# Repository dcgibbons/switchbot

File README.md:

jeepbot
=======

Jeep Bot - an intelligent accessory control system for Jeep Wranglers

In this proof of concept, the sketch assumes the following hardware has been 
configured:

  * An Arduino board with hardware SPI (any)
  * A Microchip mcp2515 CAN controller interface, such as the CAN-BUS
    shield from https://www.sparkfun.com/products/10039, wired to SPI
  * A SN74HC595 or compatible 8-bit shift register wired to SPI
  * An eight-or-more channel relay module, such as this one from http://www.sainsmart.com/8-channel-dc-5v-relay-module-for-arduino-pic-arm-dsp-avr-msp430-ttl-logic.html, that can be driven directly from GPIO logic

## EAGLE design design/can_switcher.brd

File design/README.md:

# Switchbot - The Smart Automotive Switching System (SASS)

## Overview

The "Switchbot" project is a smart switching system for automotive accessories. Imagine
having your off-road lights automatically controlled by your high-beams, or your aftermarket
LED headlights directly powered without special wiring harnesses, elimating both flicker and
swiching delays. Imagine having additional interior lighting or accessories automatically
activated whenever the car is switched on, or when the night-time interior lights are activated
by the vehicle. Imagine doing all of this without splicing any of the existing wiring. Switchbot
will do all of this, and more.

### Why is This Even Needed?

Utility vehicles frequently have many accessories installed by the owner or by vendors. These
accessories include additional lighting, recovery equipment (i.e. winches), sirens, 
radio/communication equipment, etc. Frequently, these accessories are installed by splicing
into the vehicle's own electrical wiring, which ultimately can cause system failure as 
connections fail and corrode over time. In an off-road environment, this situation is accelerated
by the harsh conditions.

In addition, vehicles today have complex electrical systems. Much of the vehicle's systems
communicate to one another using networking technologies such as a CAN bus or a LIN bus. These
networking systems cannot be used directly without adversing affecting the vehicle's operation.

Some vehicle manufacturers provide "upfitter" modules that are designed specifically for the
purpose of controlling aftermarket accessories. However, these seem to be currently limited 
only to truck vehicles, and not for off-road sport vehicles.

The marketplace has answered by providing accessory controllers that isolate the vehicle's
electrical system from accessories. Unfortunately, these modules completely isolate themselves
from the vehicle's electrical system, providing no integration features, such as automatic
light control.

The "switchbot" project aims to fill this hole in the marketplace with an intelligent and
integrated accessory control system. Initially this system will be aimed for the Jeep
Wrangler using the JK/JKU platform.

## Design

The production design of "Switchbot" will separate the system into the following primary modules:

1. A power/relay module - located in the engine bay, this module directly powers your accessories
using standard automotive relays and is the central wiring hub. Directly connected to the 
vehicle battery, it isolates all accessories from the vehicle's own electrical system.
2. A manual switch module - an optional module that provides physical switches for master overrides
for each accessory.
3. The Switchbot module - an optional module that integrates with the vehicle's electrical system
and operates accessories based on vehicle activity and user configuration.
4. Touch-screen - an optional module that provides a touch-screen interface for switches instead
of manual switches.

This design approach fulfills the following requirements for both hobbist and commerical
productization:

1. Lower price points by separating advanced features from the basics.
2. Lower price points by allowing different numbers of accessory connections in the power/relay
module. For example, the lower price module may only contain 4 switches, whereas the deluxe
module may include 8 or more.
3. Isolating vehicle-specific interfacing and software into a single module, separate from
the power/delay module, allowing easy multi-vehicle support in the future.
4. The unintelligent power/relay module can be used to provide users with their own basic
switching platform, with additional reliability and flexibility compared to the typical homegrown
solution.

### Power/Relay Module Design Considerations

The power/relay module is the hub that all aftermarket accessories will connect to. This 
module will provide each accessory connectin with an individualy fused power and ground
connection. Power to each accessory will be controlled by an external switching module.
The power/relay module will be directly connected to the battery, via a master breaker,
completely isolating accessories from the rest of the vehicle's electrical system.

The power/relay module is the simplest of all the modules in the smartbot system, but has
the most expensive components and the highest environmental demands due to its location
in the engine compartment. 

Automotive-class relays tend to be relatively expensive, ranging from $1.50 to $7.50 each.
Solid-state relays are not yet an option, as they are both too expensive and general, and
provide very limited options for high current (25a, 30a, or 40a load) applications.

While not required in the initial release of the module, the power/relay board will
include additional features such as a low-voltage cutoff circuit to prevent the vehicle's
battery from being drained.

### Switchbot Module Design Considerations

The switchbot module is ultimately a micro-controller that interfaces with the power/relay
module and with the vehicle's own communication network. On the JK platform, this means
the module should communicate to the CAN interior bus, and potentially the powertrain CAN
bus, so that it can detect when certain vehicle systems are activated, e.g. the headlamps.

Many modern micro-controllers targetted at the automotive market include CAN and/or LIN
interfaces, such as the Microchip PIC18 or the Texas Instruments C2000 families. As of
this writing, however, these MCUs are typically not cheaper than a multi-chip system
built around an MCU and a combination of a CAN controller and transceiver. Additionally,
all of the prototyping and research work has been done using ATMEGA MCUs, using the
Arduino platform, and Microchip's MCP2515 and MCP2551 CAN ICs. In the initial versions
of the smartbot system, the ATMEGA 328, the MCP2515, and the MCP2551 will be used
to lower the overall risk of the project. Future versions of find cost savings,
enhanced reliability, and increased CPU power by moving to an all-in-one MCU solution.

The JK platform has three CAN busses: the diagnostic CAN bus, the powertrain CAN bus,
and the interior CAN bus. All three busses terminate in the vehicle's TIPM module,
located in the engine compartment. While desierable, it is not practical to interface
with the busses via this module as the wiring terminals are water-resistent and 
complex.

There are two likely approaches for intefacing with the vehicle from the cabin: using
the diagnostic bus or the CAN interior bus. At first glance, the diagnostic bus would
appear ideal, but is not designed for long-running embedded applications. Additionally,
reverse engineering the necessary information available over the bus is highly time
consuming. Purchasing the same information directly from the manufacturer is out of
the range of a hobbist project, nor would it enable the project to be open-sourced.

Left with the CAN interior bus, we find that all of the information we are after is
directly available. The JK's EMIC module communicates all user activated features
to the TIPM. If the user or ambient light sensor wants the headlights on, the EMIC
makes it happen by telling the TIPM over the CAN interior bus. Switchbot can spy on
these messages and activate its own switches as needed.

The switchbot module must communicate to the power/relay module to activate each
individual accessory as needed. Two alternatives have been considered for this
communication:

1. Using a private communication channel, such as another CAN bus, between an MCU
on the power/relay module and an MCU on the switchbot module.
2. Individual switch signals to drive the relays in the power/relay module.

For the initial version, individual switch signals will be used to simplify the overall
system design and to keep costs down. Each switch signal is driven by an opticoupler 
which is in turned driven by the MCU (via a shift register IC). This will isolate the
MCU's 5v system from the 12v system needed to drive the automotive grade relays.

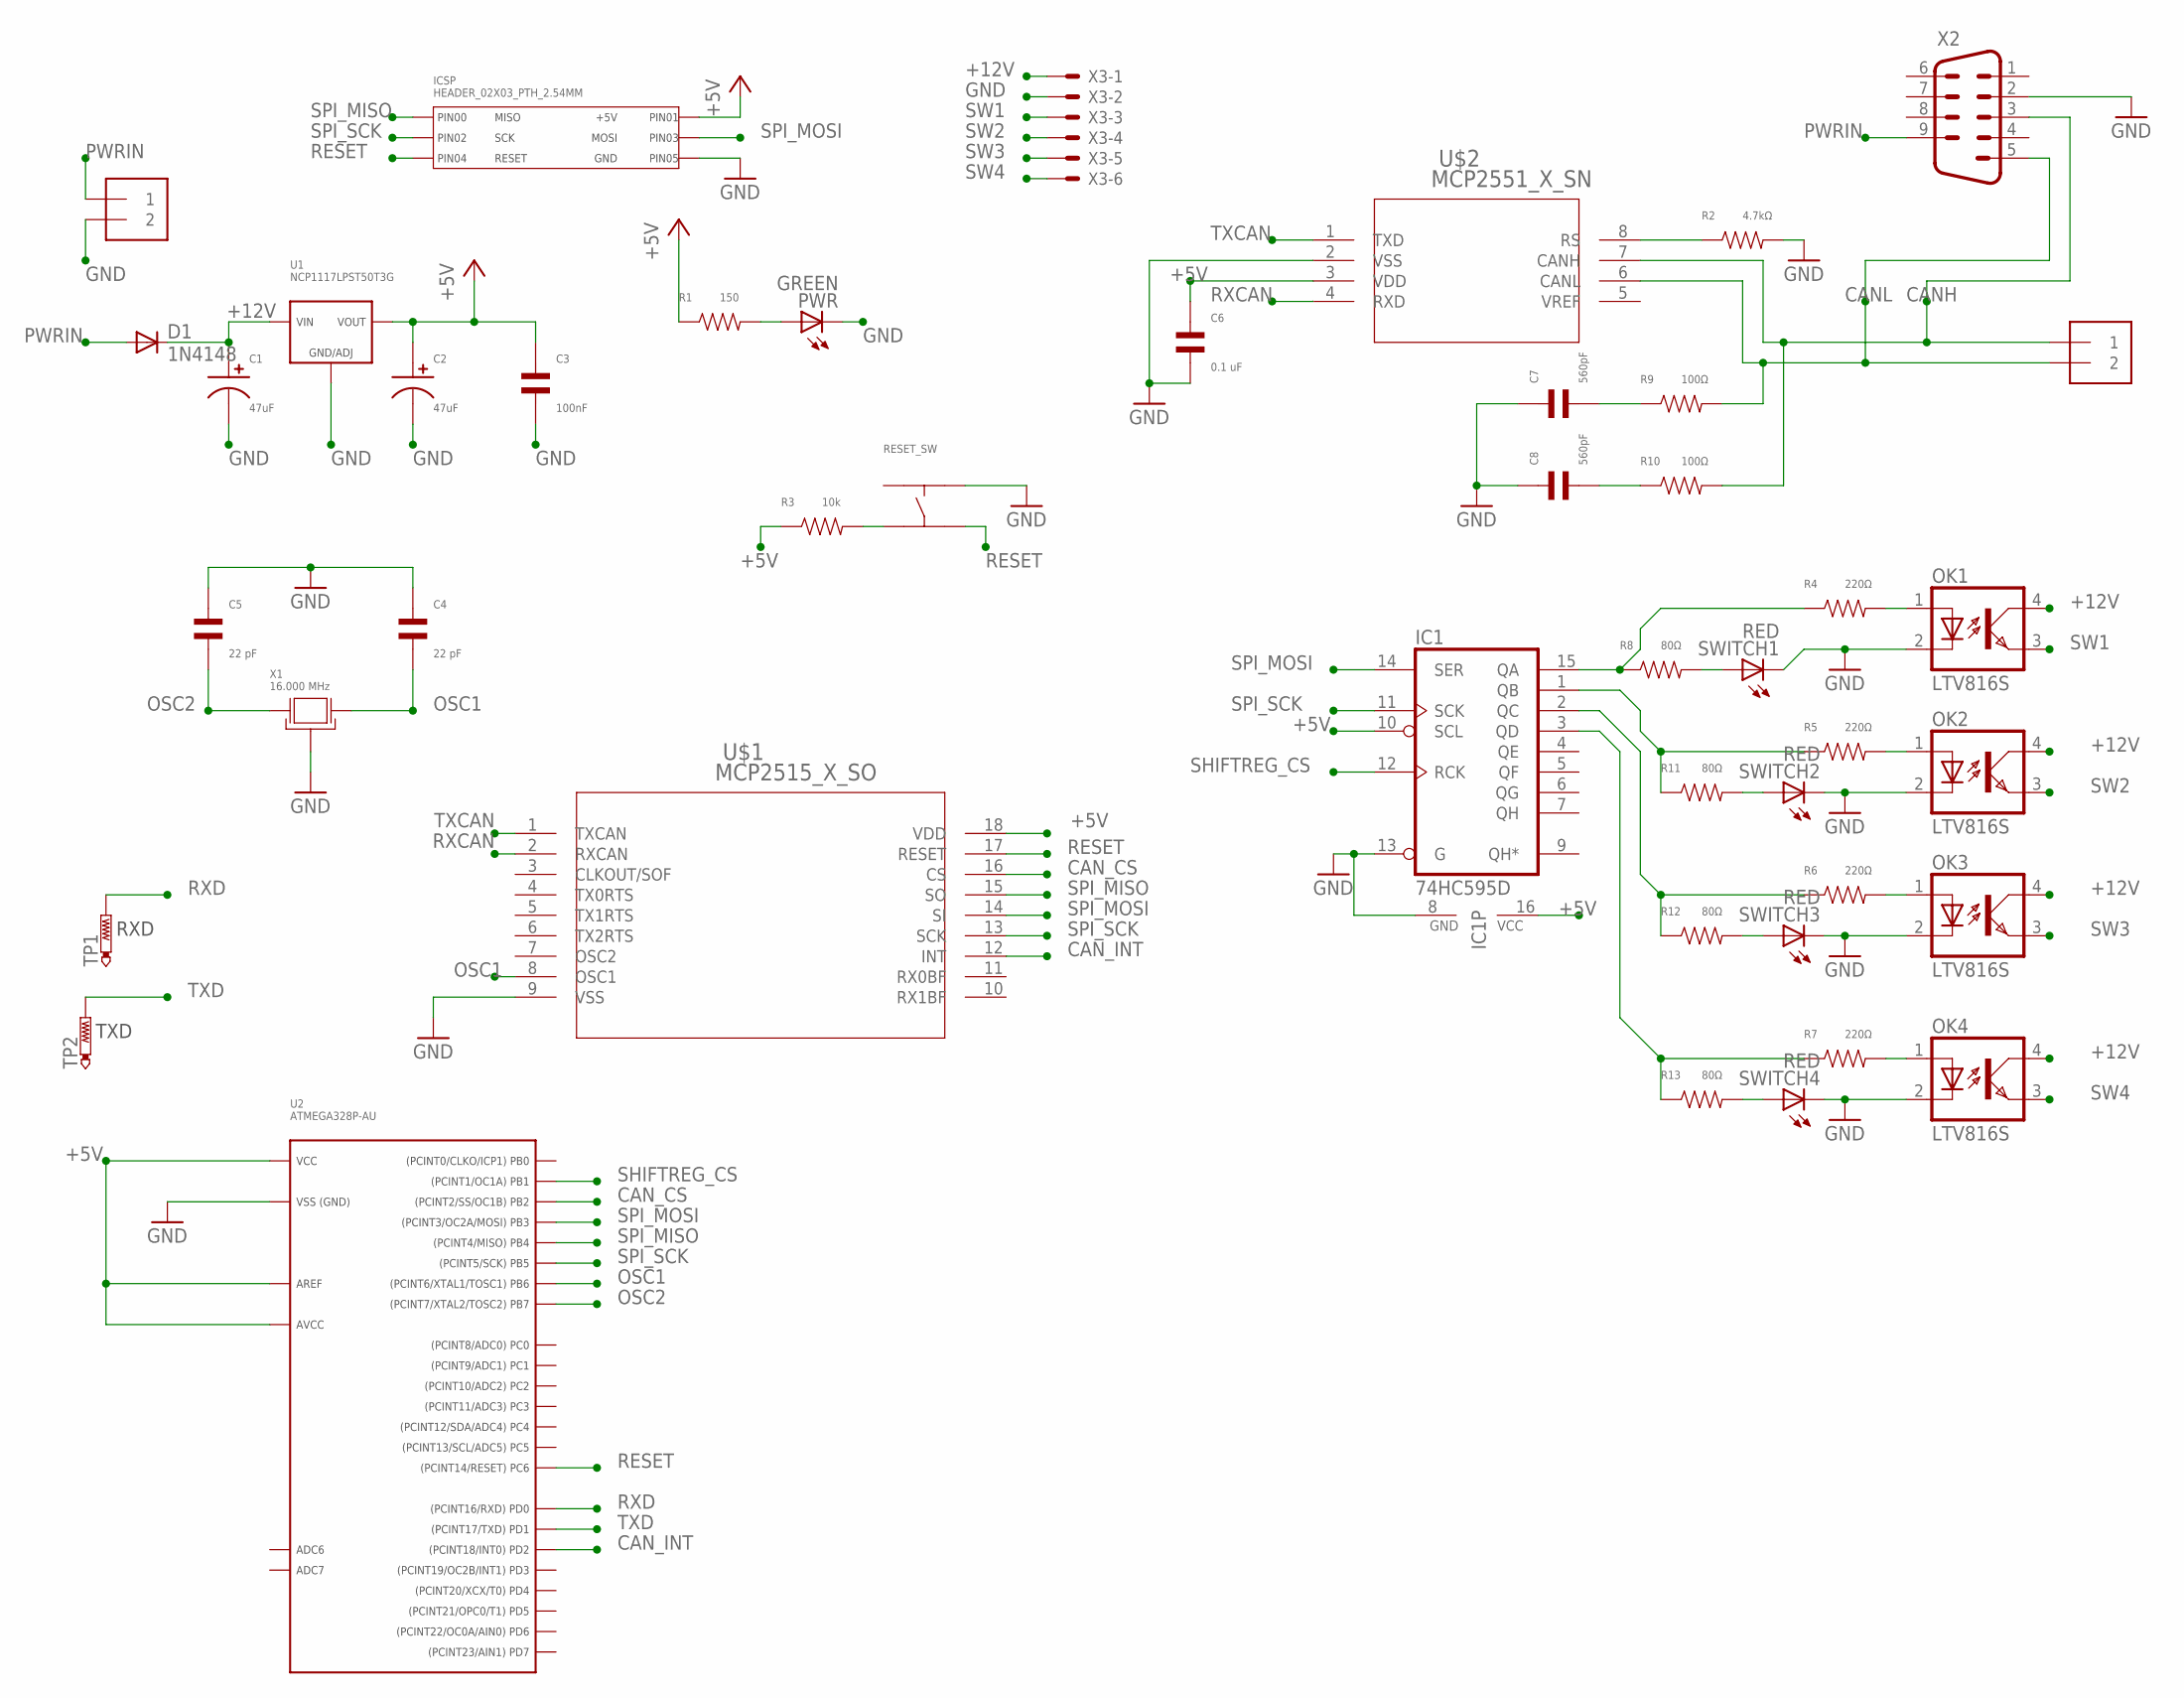
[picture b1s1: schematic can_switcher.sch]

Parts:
C1, C2: 47uF; CP6.3MM; MFG# MF-CAP-6.3MM-47uF
C3: 100nF; C0603
C4, C5: 22 pF; C0603
C6: 0.1 uF; C0603
C7, C8: 560pF; C0603; MFG# C0603C561J5GACTU
CANBUS: 1X2-3.5MM
D1: 1N4148; SMB
IC1: 74HC595D; SO16
ICSP: HEADER_02X03_PTH_2.54MM; PTH_2.54MM_02X03
J3: 1X2-3.5MM
OK1, OK2, OK3, OK4: LTV816S; SMD4; MPN LTV-816S-TA
PWR: GREEN; SML0603
R1: 150; R0603; MFG# RC0603FR-07150RL
R2: 4.7kΩ; R0603
R3: 10k; R0603
R4, R5, R6, R7: 220Ω; R0603
R8, R11, R12, R13: 80Ω; R0603
R9, R10: 100Ω; R0603
RESET_SW: TACT_6MM; TACT6MM; MFG# MF-SW-TACT-6MM
SWITCH1, SWITCH2, SWITCH3, SWITCH4: RED; SML0603
TP1, TP2: PTR1B1,27; B1,27
U1: NCP1117LPST50T3G; SOT-223-3
U2: ATMEGA328P-AU; TQFP32
U$1: MCP2515_X_SO; SOIC18_W_MC
U$2: MCP2551_X_SN; SOIC8_N_MC
X1: 16.000 MHz; 5MMX3.2MM; MFG# ASFL1-16.000MHZ-EC-T
X2: M09HP; MPN L717SDE09P1ACH
X3: 22-23-2061

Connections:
+5V: C2.P$1, C3.P$1, C6.P$1, IC1.10 (SCL), IC1.16 (VCC), ICSP.P$2 (PIN1), R1.P$1, R3.P$1, U1.P$1 (VOUT), U1.P$3 (VOUT), U2.P$4 (VCC), U2.P$6 (VCC), U2.P$18 (AVCC), U2.P$20 (AREF), U$1.18 (VDD), U$2.3 (VDD)
+12V: C1.P$1, D1.C, OK1.4 (COL), OK2.4 (COL), OK3.4 (COL), OK4.4 (COL), U1.P$4 (VIN), X3.1
CANH: CANBUS.1, R10.P$2, U$2.7 (CANH), X2.3
CANL: CANBUS.2, R9.P$2, U$2.6 (CANL), X2.5
CAN_CS: U2.P$14 (PB2), U$1.16 (CS)
CAN_INT: U2.P$32 (PD2), U$1.12 (INT)
GND: C1.P$2, C2.P$2, C3.P$2, C4.P$1, C5.P$1, C6.P$2, C7.P$1, C8.P$1, IC1.8 (GND), IC1.13 (G), ICSP.P$6 (PIN5), J3.2, OK1.2 (C), OK2.2 (C), OK3.2 (C), OK4.2 (C), PWR.C, R2.P$2, RESET_SW.P$2, SWITCH1.C, SWITCH2.C, SWITCH3.C, SWITCH4.C, U1.P$2 (GND/ADJ), U2.P$3 (GND), U2.P$5 (GND), U2.P$21 (GND), U$1.9 (VSS), U$2.2 (VSS), X1.P$2 (GND), X1.P$4 (GND), X2.2, X3.2
unnamed: PWR.A, R1.P$2
unnamed: R2.P$1, U$2.8 (RS)
unnamed: R3.P$2, RESET_SW.P$3
unnamed: R8.P$2, SWITCH1.A
unnamed: R11.P$2, SWITCH2.A
unnamed: R12.P$2, SWITCH3.A
unnamed: R13.P$2, SWITCH4.A
unnamed: OK4.1 (A), R7.P$2
unnamed: OK3.1 (A), R6.P$2
unnamed: OK2.1 (A), R5.P$2
unnamed: OK1.1 (A), R4.P$2
unnamed: IC1.15 (QA), R4.P$1, R8.P$1
unnamed: IC1.1 (QB), R5.P$1, R11.P$1
unnamed: IC1.2 (QC), R6.P$1, R12.P$1
unnamed: IC1.3 (QD), R7.P$1, R13.P$1
unnamed: C7.P$2, R9.P$1
unnamed: C8.P$2, R10.P$1
OSC1: C4.P$2, U2.P$7 (PB6), U$1.8 (OSC1), X1.P$3 (X1)
OSC2: C5.P$2, U2.P$8 (PB7), X1.P$1 (X0)
PWRIN: D1.A, J3.1, X2.9
RESET: ICSP.P$5 (PIN4), RESET_SW.P$4, U2.P$29 (PC6), U$1.17 (RESET)
RXCAN: U$1.2 (RXCAN), U$2.4 (RXD)
RXD: TP1.TP, U2.P$30 (PD0)
SHIFTREG_CS: IC1.12 (RCK), U2.P$13 (PB1)
SPI_MISO: ICSP.P$1 (PIN0), U2.P$16 (PB4), U$1.15 (SO)
SPI_MOSI: IC1.14 (SER), ICSP.P$4 (PIN3), U2.P$15 (PB3), U$1.14 (SI)
SPI_SCK: IC1.11 (SCK), ICSP.P$3 (PIN2), U2.P$17 (PB5), U$1.13 (SCK)
SW1: OK1.3 (EMIT), X3.3
SW2: OK2.3 (EMIT), X3.4
SW3: OK3.3 (EMIT), X3.5
SW4: OK4.3 (EMIT), X3.6
TXCAN: U$1.1 (TXCAN), U$2.1 (TXD)
TXD: TP2.TP, U2.P$31 (PD1)

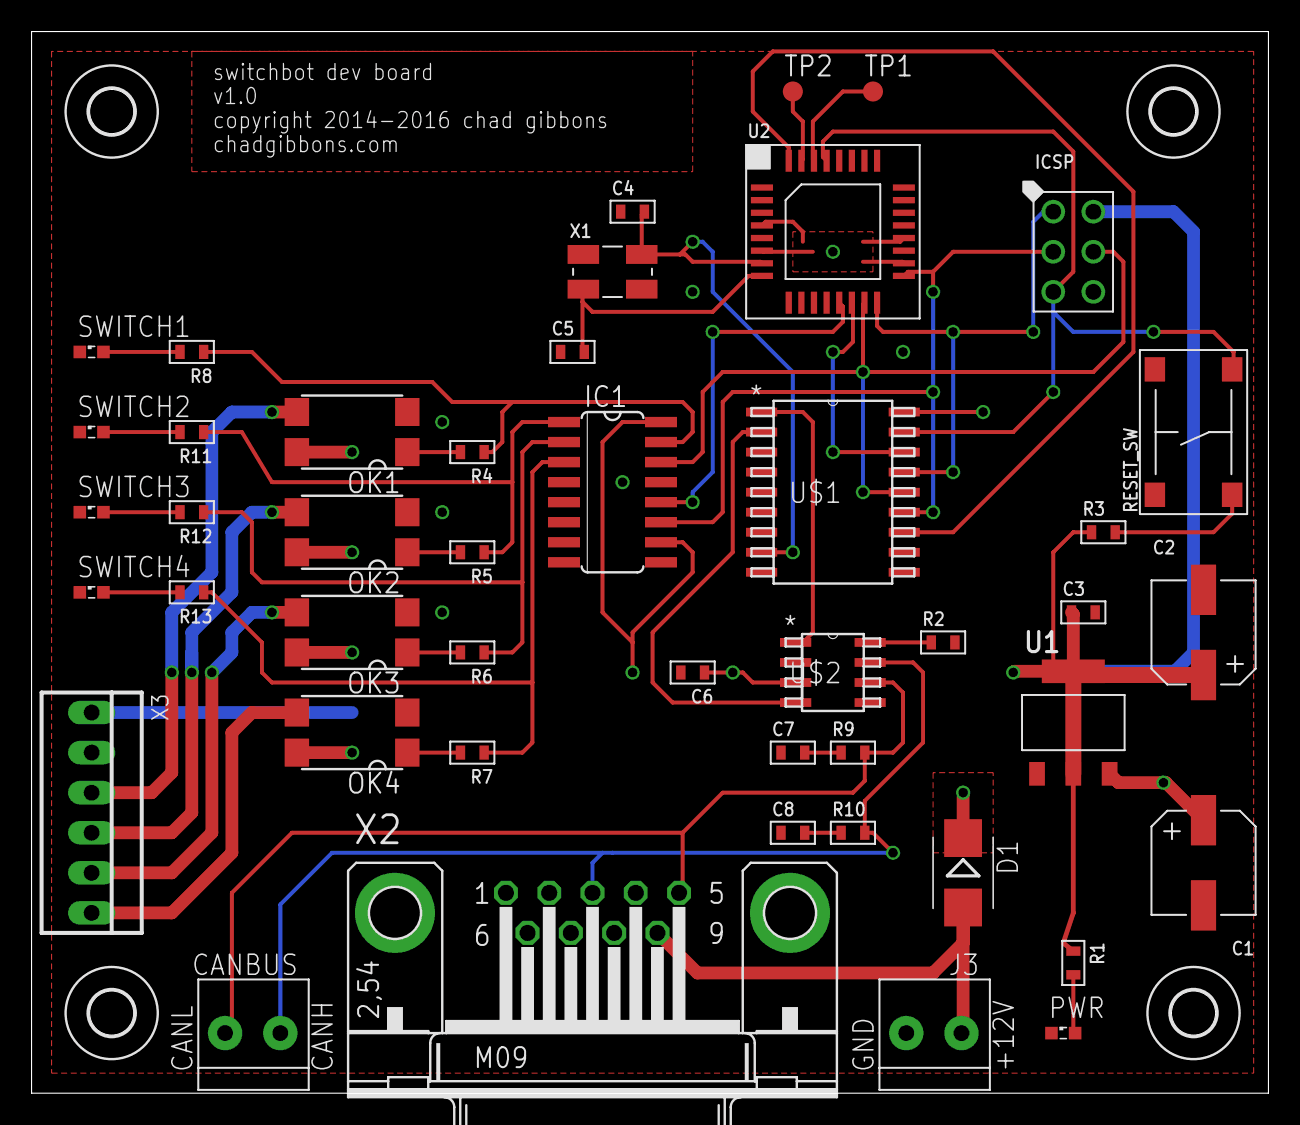
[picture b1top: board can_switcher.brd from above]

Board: 2 copper layers, 78.4 x 67.3 mm, 49 parts (0 on the bottom side), 40 nets.

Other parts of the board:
U$3, U$4, U$5, U$6: 2,8

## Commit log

2014-01-09 initial version of proof of concept #1
2014-01-09 update copyright name
2014-01-09 add block diagram of proof of concept
2015-12-23 can switcher v1.0 protoype design
2015-12-23 update design files to get text on proper silkscreen layer; try adding MFG# to various parts
2015-12-29 add production design discussion and diagrams
2019-04-25 update gitignore

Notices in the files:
design/can_switcher.brd:
copyright 2014-2016 chad gibbons
